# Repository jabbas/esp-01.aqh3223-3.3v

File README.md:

# esp01-aqh3223-hat

# Schema

# PCB

# Render front

# Render back

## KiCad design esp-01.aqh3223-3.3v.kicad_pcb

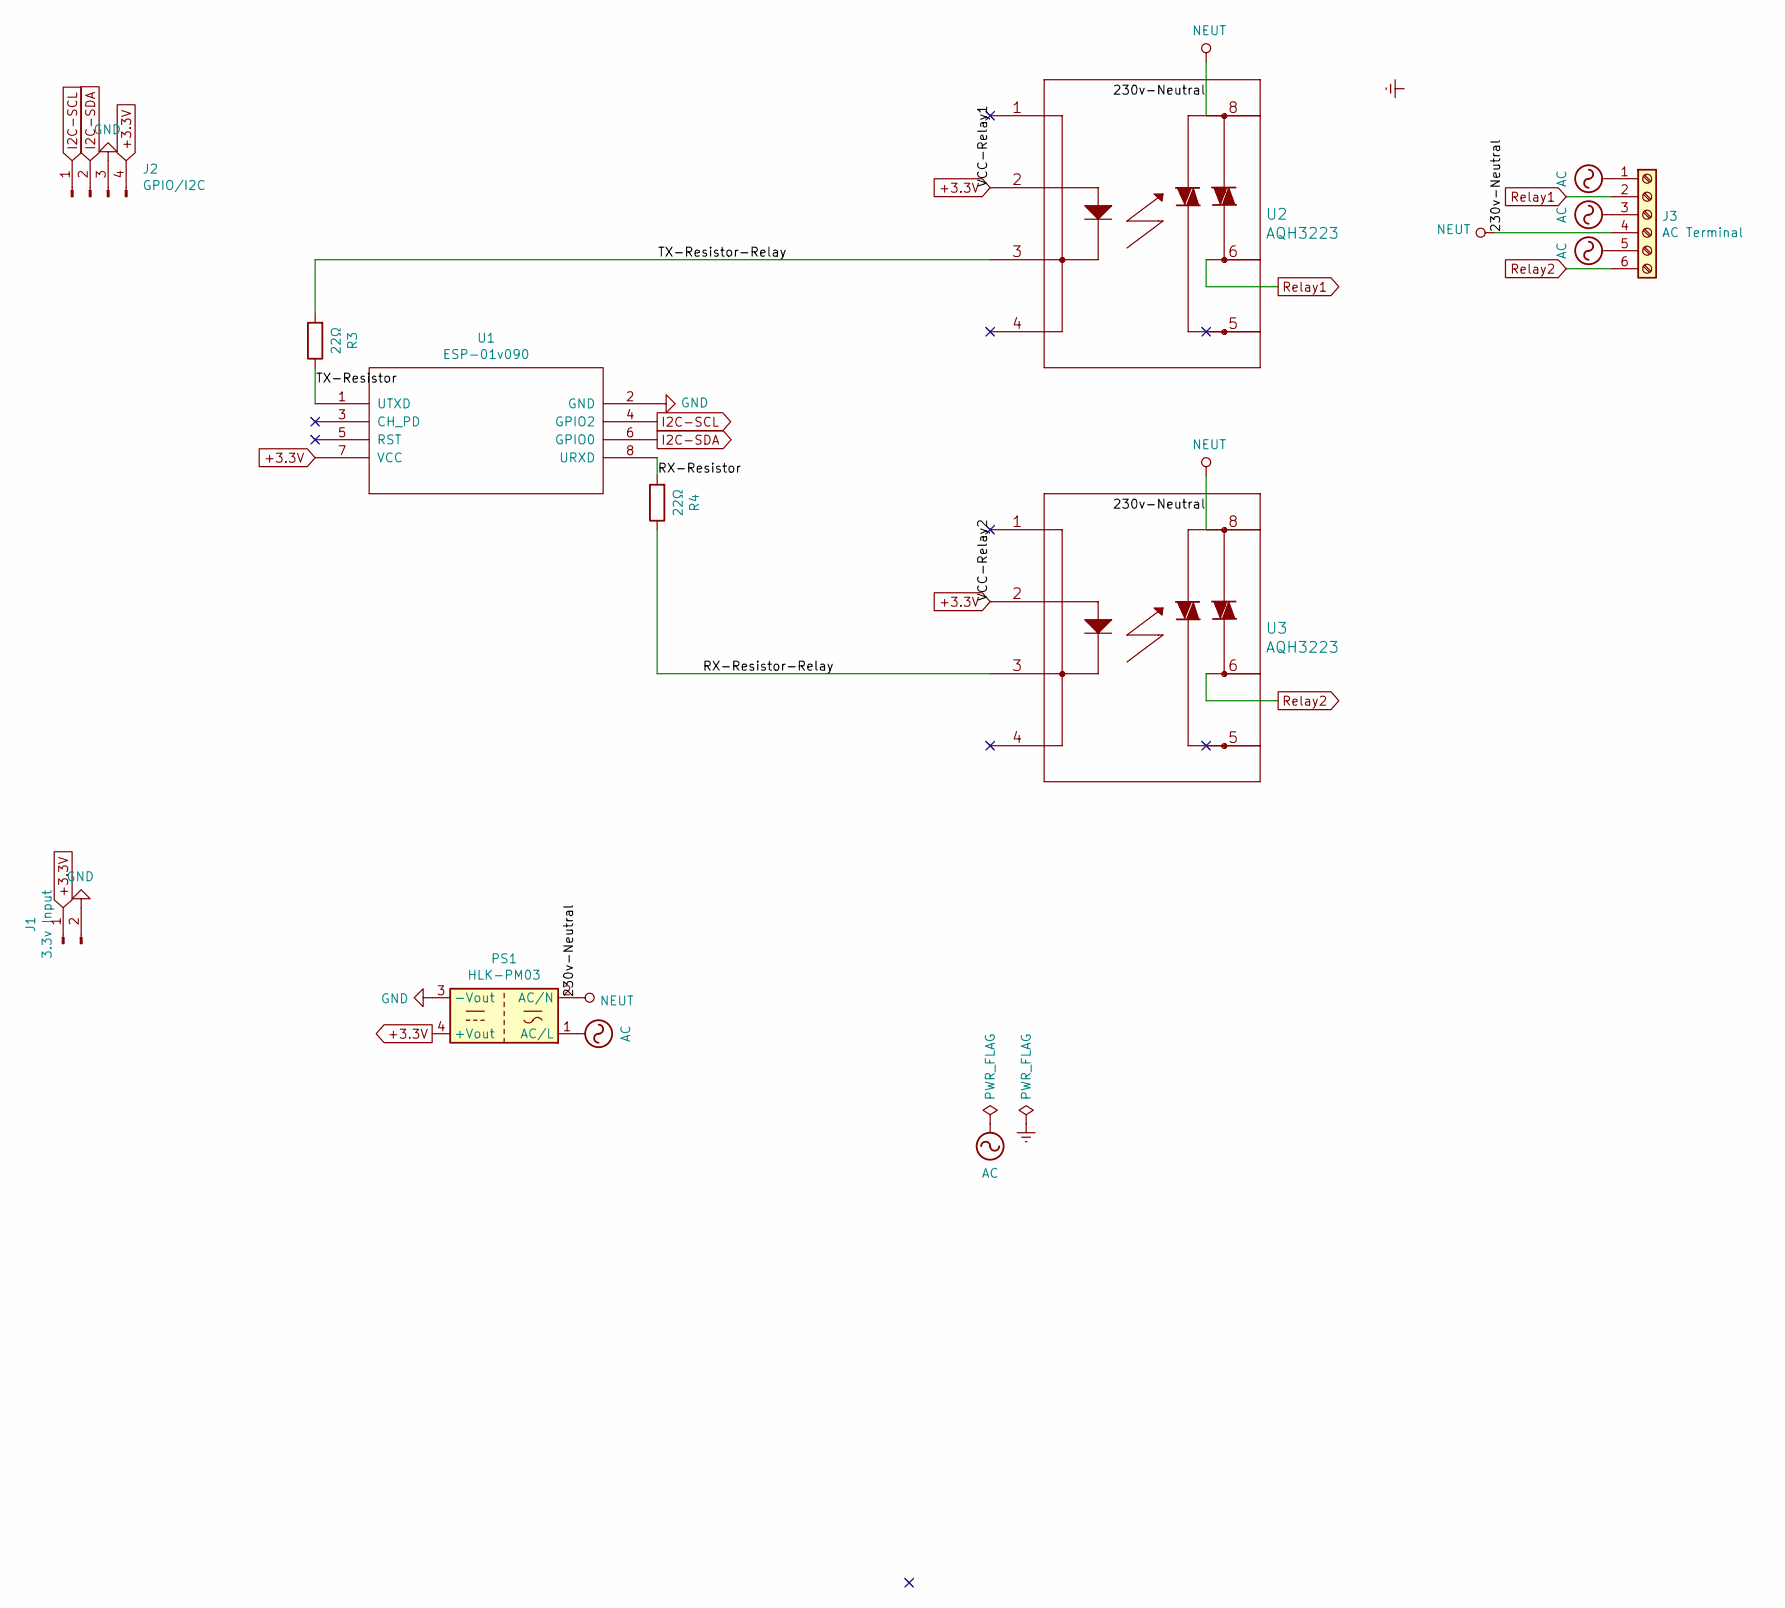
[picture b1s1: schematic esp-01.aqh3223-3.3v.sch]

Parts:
J1: 3.3v Input; PinSocket_1x02_P2.54mm_Vertical_SMD_Pin1Left
J2: GPIO/I2C; PinSocket_1x04_P2.54mm_Vertical_SMD_Pin1Left
J3: AC Terminal; TerminalBlock_bornier-6_P5.08mm
PS1: HLK-PM03; Converter_ACDC_HiLink_HLK-PMxx
R3, R4: 22Ω; R_0805_2012Metric_Pad1.15x1.40mm_HandSolder
U1: ESP-01v090; ESP-01-SMD
U2, U3: AQH3223; AQH3223AX

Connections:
+3.3V: J1.1, J2.4, PS1.4 (+Vout), U1.7 (VCC), U2.2, U3.2
/RX-Resistor: R4.2, U1.8 (URXD)
/RX-Resistor-Relay: R4.1, U3.3
/TX-Resistor: R3.1, U1.1 (UTXD)
/TX-Resistor-Relay: R3.2, U2.3
AC: J3.1, J3.3, J3.5, PS1.1 (AC/L)
GND: J1.2, J2.3, PS1.3 (-Vout), U1.2 (GND)
I2C-SCL: J2.1, U1.4 (GPIO2)
I2C-SDA: J2.2, U1.6 (GPIO0)
NEUT: J3.4, PS1.2 (AC/N), U2.8, U3.8
Relay1: J3.2, U2.6
Relay2: J3.6, U3.6

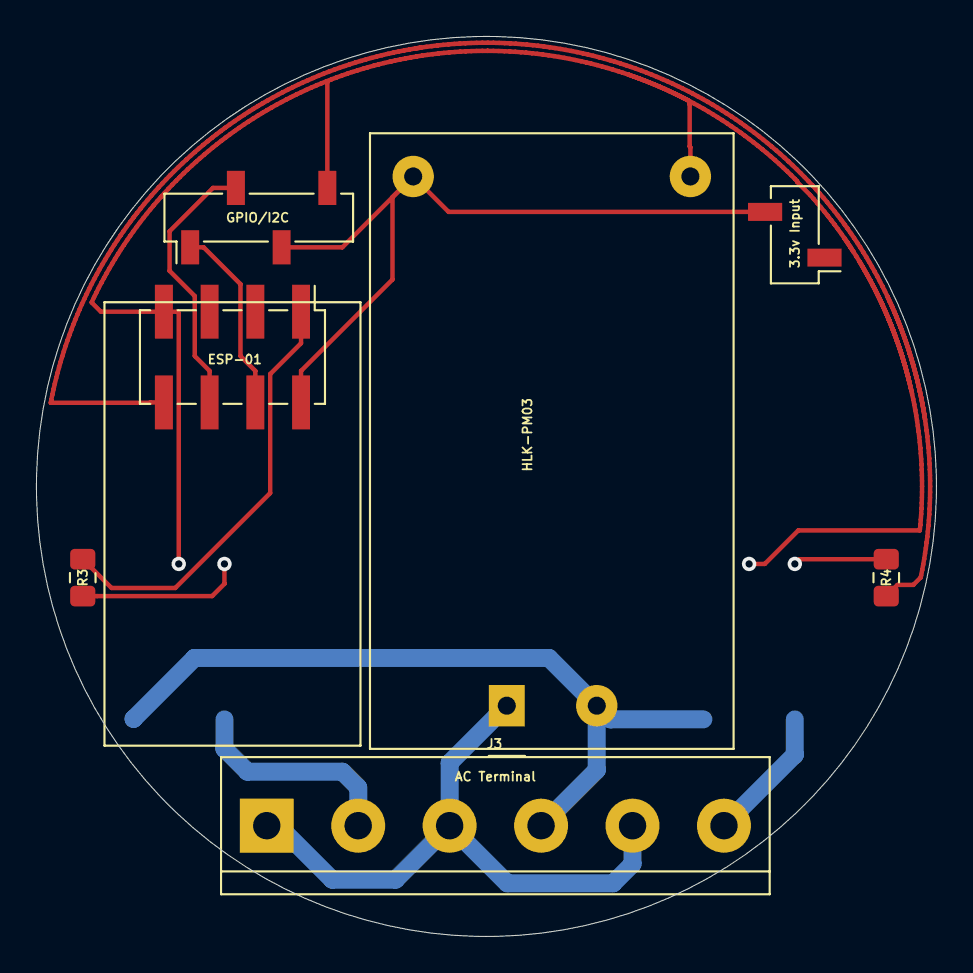
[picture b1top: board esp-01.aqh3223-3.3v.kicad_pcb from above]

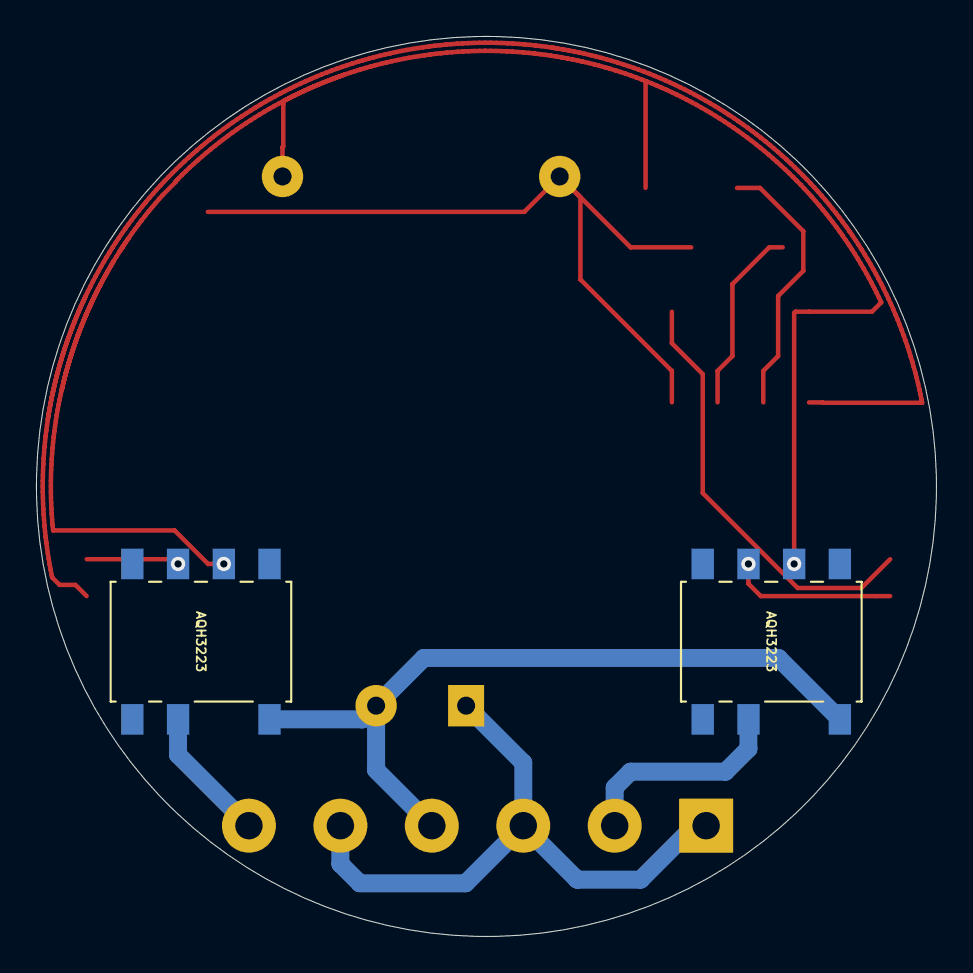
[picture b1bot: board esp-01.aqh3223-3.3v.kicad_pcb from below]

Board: 2 copper layers, 50.0 x 50.0 mm, 9 parts (2 on the bottom side), 12 nets.

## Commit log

2020-08-25 adds README.md
2020-08-25 typo
